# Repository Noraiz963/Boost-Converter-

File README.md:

# Boost Converter (XL6009)

A DC-DC step-up (boost) converter designed in KiCad, built around the **XL6009** switching regulator IC — takes a lower input DC voltage and boosts it to a higher, adjustable regulated output voltage.

## Why This Exists

Many projects have a power source that's lower than what a circuit actually needs — e.g. boosting a single Li-ion cell (~3.7V) up to 12V, or a 5V USB source up to 9V/12V for other electronics. A linear regulator can't do this (it can only step voltage *down*), so a switching boost converter is required. This board uses the XL6009 to do that conversion efficiently, with an adjustable output via an onboard potentiometer.

## Circuit Overview

- **Input**: J1/J2 2-pin connector bringing in input DC voltage and GND
- **Input filtering**: C1 (47µF) for bulk smoothing, C2 (1µF) for high-frequency noise filtering
- **Core regulator**: XL6009 (VR1) boost converter IC — handles the actual switching/voltage step-up
- **Inductor**: L1 (33µH, 4A) — energy storage element central to the boost topology
- **Rectifier diode**: D1 (SS34 Schottky) — low forward-drop, fast-switching diode for the output rectification path
- **Feedback/voltage adjustment**: RV1 (potentiometer) + R1 (1kΩ) form a feedback divider into the XL6009's FB pin, letting you tune the output voltage
- **Output filtering**: C3 (1µF) and C4 (220µF) smooth the regulated output
- **Output**: J3/J4 2-pin connector delivering the boosted, regulated DC voltage to the load

## Signal Flow (Concept)

**Energy conversion path:**
1. Input DC voltage enters through J1/J2, filtered by C1/C2.
2. The XL6009's internal switch rapidly turns ON/OFF at the SW pin, connected to inductor L1.
3. **Switch ON:** Current flows from VIN through L1, storing energy in its magnetic field. D1 blocks reverse current into the output during this phase.
4. **Switch OFF:** L1's stored energy releases, and its voltage adds on top of VIN, pushing current through D1 into the output capacitors at a higher voltage than the input.
5. This switching repeats at high frequency (hundreds of kHz), continuously pumping energy to the output.
6. C3/C4 smooth the resulting output into clean, stable DC.
7. Regulated output is delivered to the load via J3/J4.

**Feedback / voltage regulation:**
- The FB pin on the XL6009 monitors a scaled-down sample of the output voltage via the RV1/R1 resistor divider.
- If output voltage drifts from the set point, the XL6009 adjusts its switching duty cycle (how long the switch stays ON per cycle) to correct it.
- Adjusting RV1 changes the divider ratio, which shifts what output voltage the chip regulates to — this is how the output voltage becomes user-adjustable.

**Enable / control:**
- The EN pin is tied active, so the regulator runs continuously once powered. (Can be repurposed for external ON/OFF control if needed.)

**Ground referencing:**
- GND is shared across input, IC, and output sections — required for both the switching regulation loop and correct feedback sensing to function properly.

## Schematic
.png)

## PCB Layout
.png)

## 3D Render
.png)

## Bill of Materials

| Ref | Component | Value |
|-----|-----------|-------|
| J1, J2 | Input Connector (2x 1-pin) | — |
| J3, J4 | Output Connector (2x 1-pin) | — |
| VR1 | Boost Converter IC | XL6009 |
| L1 | Inductor | 33µH, 4A |
| D1 | Schottky Diode | SS34 |
| RV1 | Potentiometer (feedback adjust) | — |
| R1 | Resistor | 1kΩ |
| C1 | Capacitor (input bulk) | 47µF |
| C2 | Capacitor (input HF filter) | 1µF |
| C3 | Capacitor (output HF filter) | 1µF |
| C4 | Capacitor (output bulk) | 220µF |

## Specifications

| Parameter | Value |
|---|---|
| Topology | Boost (step-up) |
| Regulator IC | XL6009 |
| Inductor | 33µH / 4A |
| Output adjustment | Via onboard potentiometer (RV1) |
| Rectifier | SS34 Schottky diode |

> ⚠️ Always verify output voltage with a multimeter before connecting a load — adjust RV1 to your target voltage first, and stay within the XL6009's rated input/output limits and current capacity of L1/D1.

## Tools Used
- KiCad 10.0.4 (schematic capture, PCB layout, 3D visualization)

## Status
Completed schematic design.

## Notes
Built as a learning project to understand switching boost converter topology, inductor-based energy storage, and feedback-based voltage regulation — a practical, reusable module for future projects needing a higher voltage rail than the available supply.

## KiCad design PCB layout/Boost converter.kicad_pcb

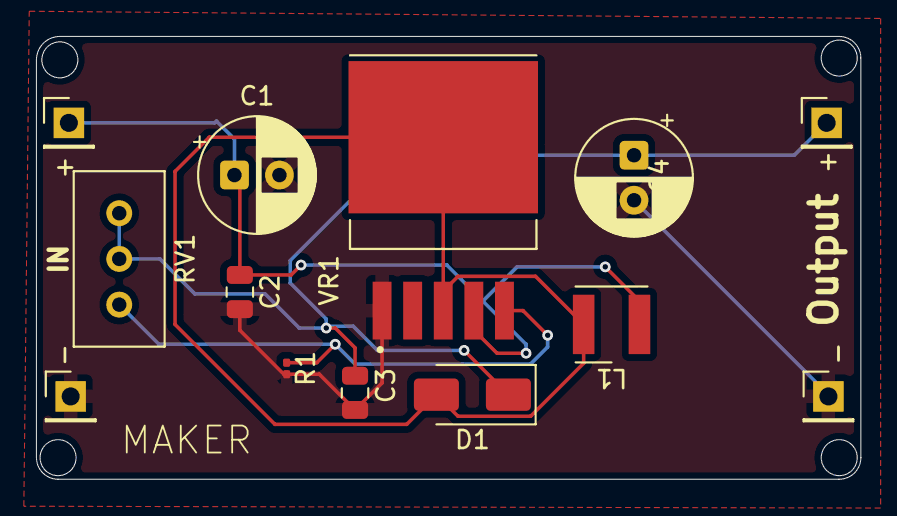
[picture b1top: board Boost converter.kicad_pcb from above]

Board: 2 copper layers, 45.8 x 24.6 mm, 13 parts (0 on the bottom side), 5 nets.

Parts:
+: Conn_01x01_Pin; PinHeader_1x01_P2.54mm_Vertical
+#2: Conn_01x01_Pin; PinHeader_1x01_P2.54mm_Vertical
-: Conn_01x01_Pin; PinHeader_1x01_P2.54mm_Vertical
C1: 47uF; CP_Radial_D6.3mm_P2.50mm
C2, C3: 1uF; C_0805_2012Metric
C4: 220uF; CP_Radial_D6.3mm_P2.50mm
D1: SS34; D_SMA
L1: 33uh/4A; L_Wurth_WE-LQSH-4020
R1: 1K; R_0201_0603Metric
RV1: 13.8K; Potentiometer_Bourns_3296W_Vertical
VR1: XL6009; DPAK170P1435X465-6N
_: Conn_01x01_Pin; PinHeader_1x01_P2.54mm_Vertical

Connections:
GND: -.1 (Pin_1_1), C1.2, C2.2, C3.2, C4.2, R1.2, VR1.1 (GND), _.1 (Pin_1_1)
unnamed: D1.2 (A), L1.2, VR1.3 (SW), VR1.6 (SW)
unnamed: +#2.1 (Pin_1_1), C3.1, C4.1, D1.1 (K), RV1.2, RV1.3
unnamed: +.1 (Pin_1_1), C1.1, C2.1, L1.1, VR1.4 (VIN)
unnamed: R1.1, RV1.1, VR1.5 (FB)
